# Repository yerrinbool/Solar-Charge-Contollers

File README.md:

# Solar Charge Contollers
Micro Controller based Solar Charge Controllers

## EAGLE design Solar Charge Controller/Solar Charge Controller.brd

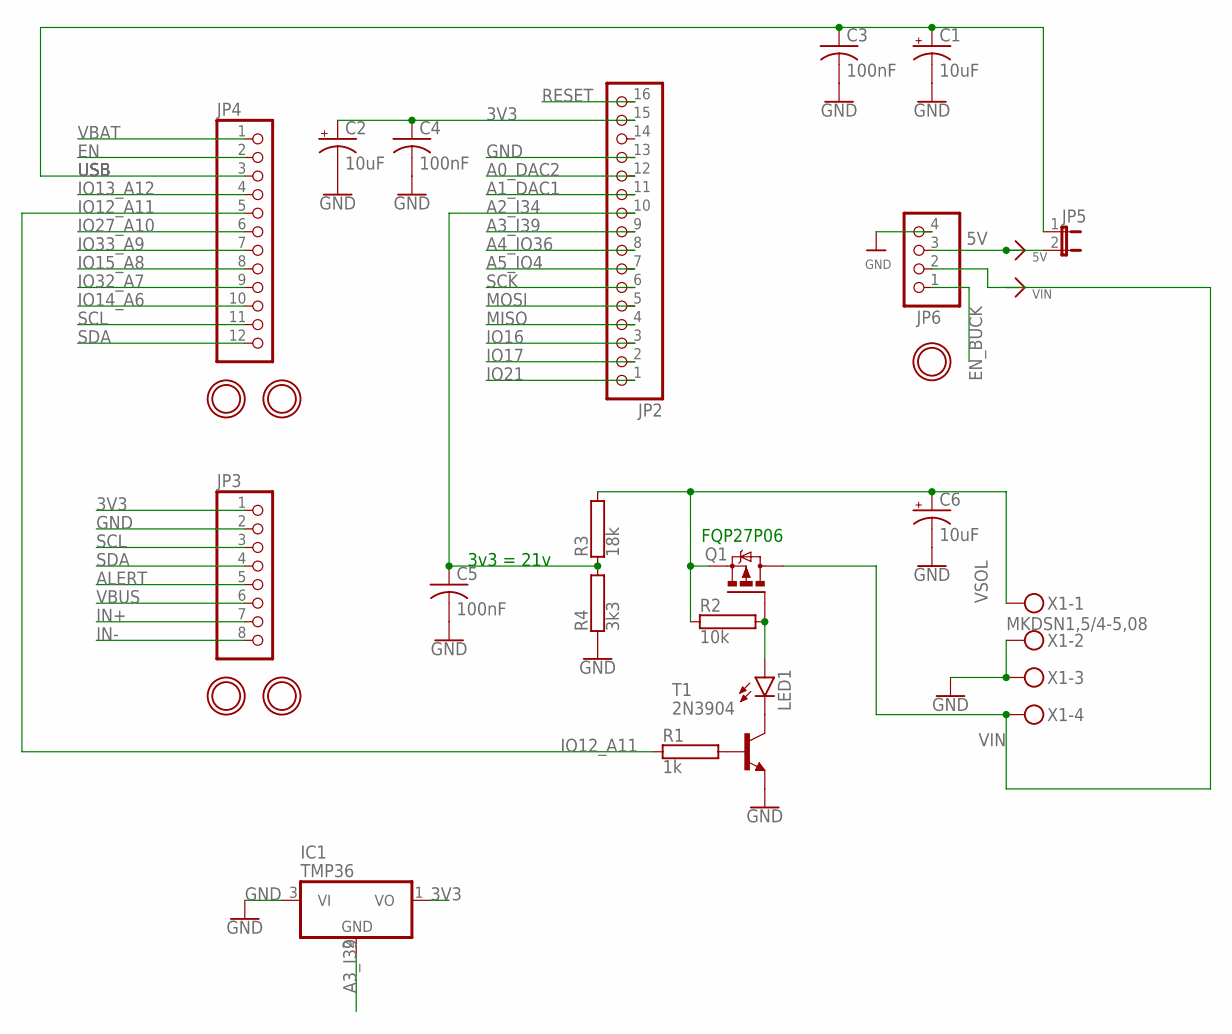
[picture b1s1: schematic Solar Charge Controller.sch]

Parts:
C1, C2, C6: 10uF; E2,5-5
C3, C4, C5: 100nF; C025-024X044
IC1: TMP36; TO92
JP2: HEADER-1X16_MIN; 1X16_ROUND_MIN
JP3: HEADER-1X870MIL; 1X08_ROUND_70
JP4: HEADER-1X12_MIN; 1X12_ROUND_MIN
JP5: JP1E; JP1
JP6: HEADER-1X4ROUND; 1X04_ROUND
LED1: LED3MM
Q1: FQP27P06; TO220BV
R1: 1k; RS1/4
R2: 10k; RS1/4
R3: 18k; RS1/4
R4: 3k3; RS1/4
T1: 2N3904; TO92
U$2, U$3, U$4, U$5, U$12: MOUNTINGHOLE2.5; MOUNTINGHOLE_2.5_PLATED
X1: MKDSN1,5/4-5,08

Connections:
3V3: C2.+, C4.1, IC1.1 (VO), JP2.15, JP3.1
5V: JP5.2, JP6.3
A0_DAC2: JP2.12
A1_DAC1: JP2.11
A2_I34: C5.1, JP2.10, R3.1, R4.2
A3_I39: IC1.2 (GND), JP2.9
A4_IO36: JP2.8
A5_IO4: JP2.7
ALERT: JP3.5
EN: JP4.2
EN_BUCK: JP6.1
GND: C1.-, C2.-, C3.2, C4.2, C5.2, C6.-, IC1.3 (VI), JP2.13, JP3.2, JP6.4, R4.1, T1.3 (E), X1.2, X1.3
IN+: JP3.7
IN-: JP3.8
IO12_A11: JP4.5, R1.1
IO13_A12: JP4.4
IO14_A6: JP4.10
IO15_A8: JP4.8
IO16: JP2.3
IO17: JP2.2
IO21: JP2.1
IO27_A10: JP4.6
IO32_A7: JP4.9
IO33_A9: JP4.7
MISO: JP2.4
MOSI: JP2.5
unnamed: LED1.A, Q1.G, R2.2
unnamed: LED1.K (C), T1.1 (C)
unnamed: R1.2, T1.2 (B)
RESET: JP2.16
SCK: JP2.6
SCL: JP3.3, JP4.11
SDA: JP3.4, JP4.12
USB: C1.+, C3.1, JP4.3, JP5.1
VBAT: JP4.1
VBUS: JP3.6
VIN: JP6.2, Q1.D, X1.4
VSOL: C6.+, Q1.S, R2.1, R3.2, X1.1

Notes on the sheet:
3v3 = 21v

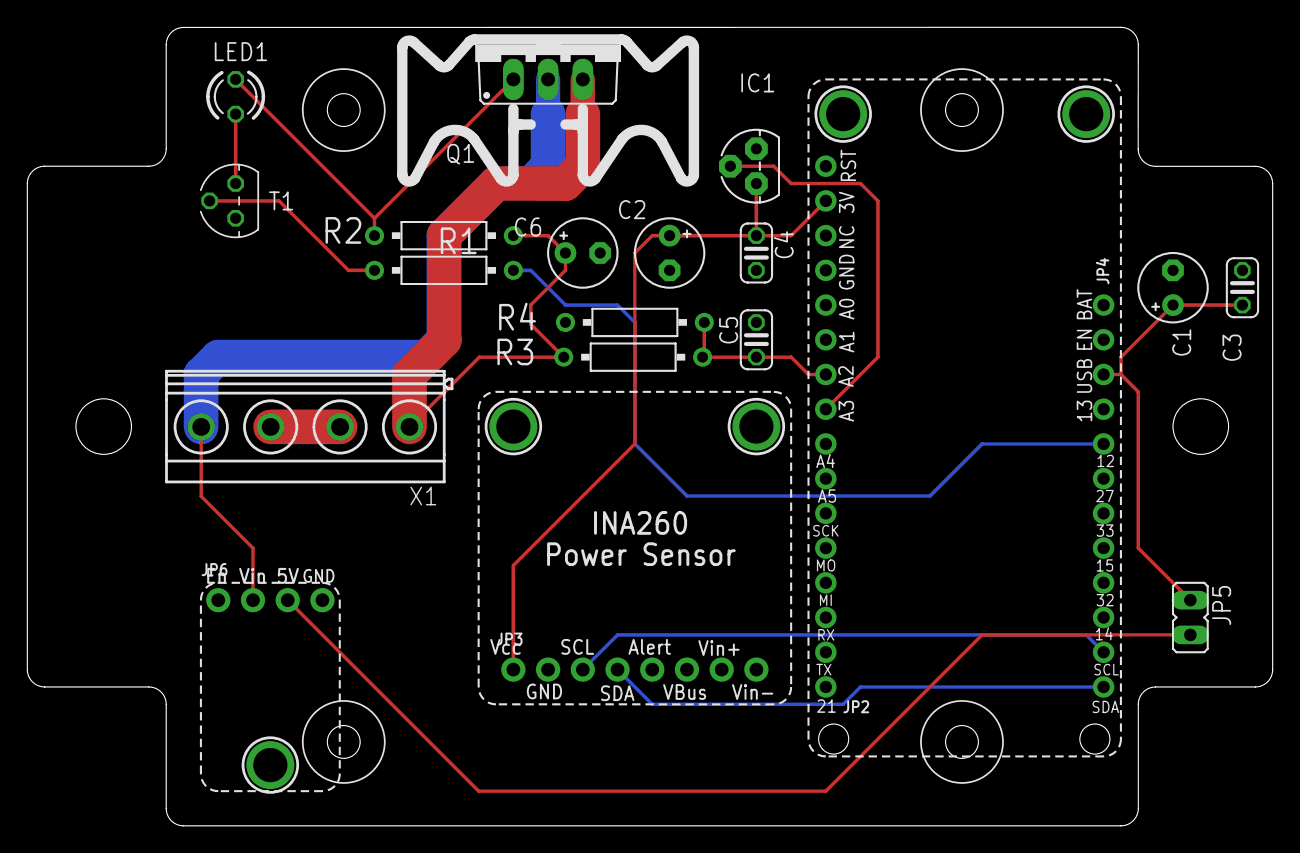
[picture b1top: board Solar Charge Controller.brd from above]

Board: 2 copper layers, 91.1 x 58.4 mm, 27 parts (0 on the bottom side), 14 nets.

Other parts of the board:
E$1: ENCLOSURE_MOUNTING
U$1: PF752

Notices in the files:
parts and their libraries:
microbuilder: This work is placed in the public domain, and may be freely used for commercial and non-commercial work with the following conditions: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
SparkFun-PowerSymbols: Licensing: Creative Commons ShareAlike 4.0 International - https://creativecommons.org/licenses/by-sa/4.0
